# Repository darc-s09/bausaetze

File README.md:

Bausätze des OV S09
===================

Seit mehreren Jahren haben wir im Ortsverband verschiedene
Bastelaktivitäten laufen, vorranging finden diese bei Veranstaltungen
der "Technischen Sammlungen Dresden" statt, in deren Räumen sich
unsere Klubstation DL0TSD befindet.

Während der Bausatz des LED-Thermometers sein eigenes Repository hier
besitzt, hatten wir die Software und auch Dokumentation für andere
Bausätze historisch auf einem privaten Openproject-Server gehostet.
Von dort wurden sie hier nach Github migriert.

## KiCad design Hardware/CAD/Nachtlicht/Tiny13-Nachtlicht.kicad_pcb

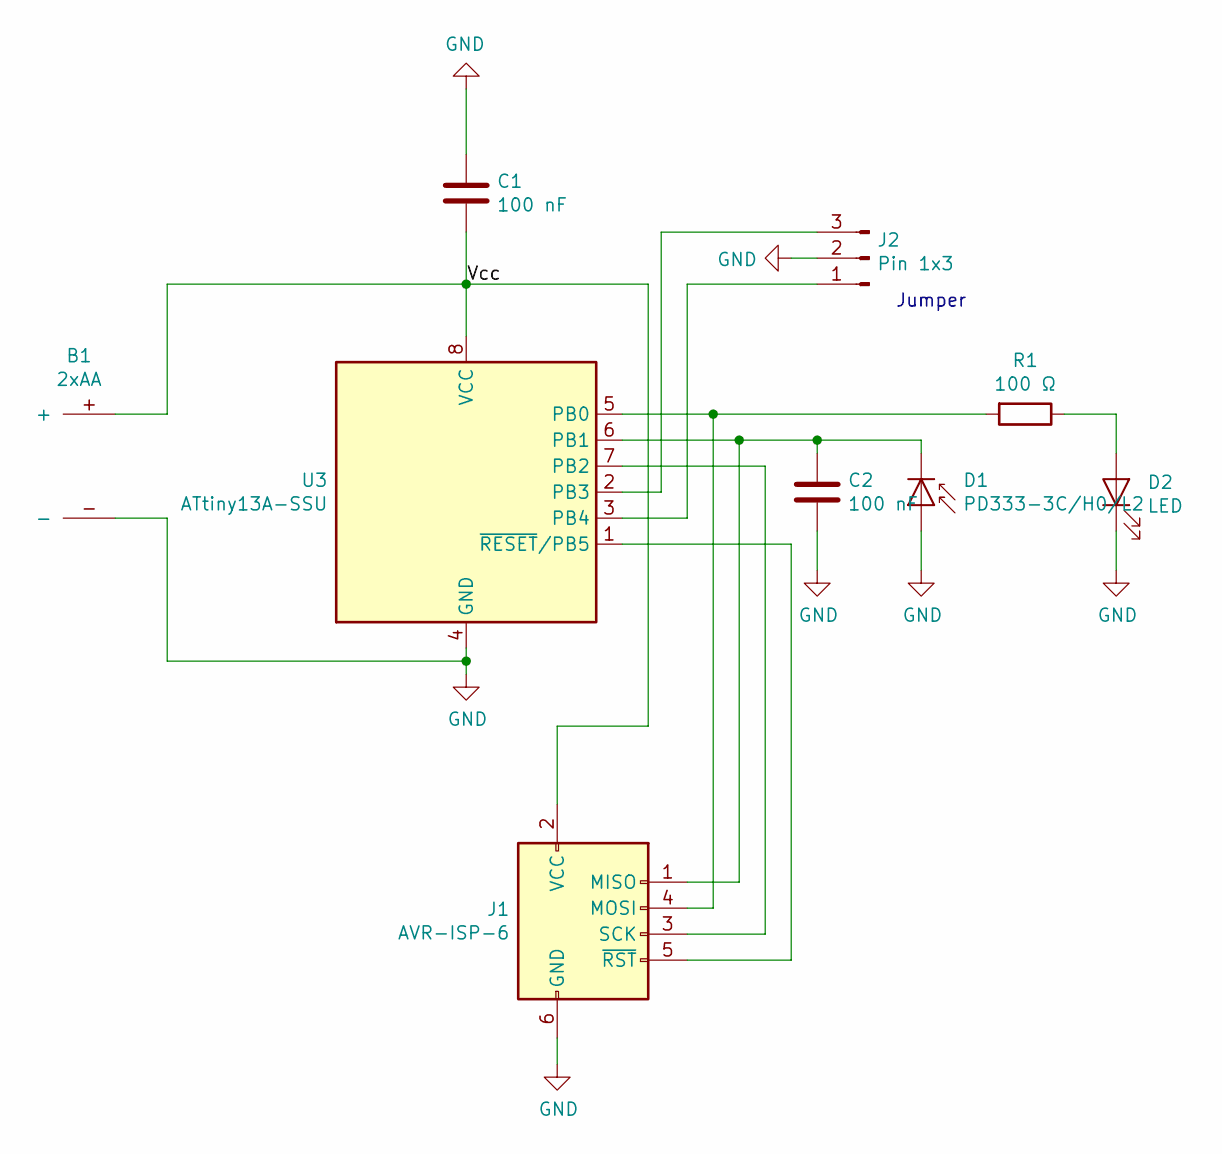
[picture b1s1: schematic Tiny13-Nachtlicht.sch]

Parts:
B1: 2xAA; 2xAA-standing
C1, C2: 100 nF; C_0805_HandSoldering
D1: PD333-3C/H0/L2; LED-5MM
D2: LED; LED-5MM
J1: AVR-ISP-6; Pin_Header_Straight_2x03
J2: Pin 1x3; Pin_Header_Straight_1x03
R1: 100 Ω; R_0805_HandSoldering
U3: ATtiny13A-SSU; SOIC-8_3.9x4.9mm_P1.27mm

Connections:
/Vcc: B1.+, C1.1, J1.2 (VCC), U3.8 (VCC)
GND: B1.-, C1.2, C2.2, D1.2 (A), D2.1 (K), J1.6 (GND), J2.2, U3.4 (GND)
unnamed: C2.1, D1.1 (K), J1.1 (MISO), U3.6 (PB1)
unnamed: D2.2 (A), R1.1
unnamed: J1.3 (SCK), U3.7 (PB2)
unnamed: J1.4 (MOSI), R1.2, U3.5 (PB0)
unnamed: J1.5 (~RST), U3.1 (~RESET~/PB5)
unnamed: J2.1, U3.3 (PB4)
unnamed: J2.3, U3.2 (PB3)

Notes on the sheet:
Jumper

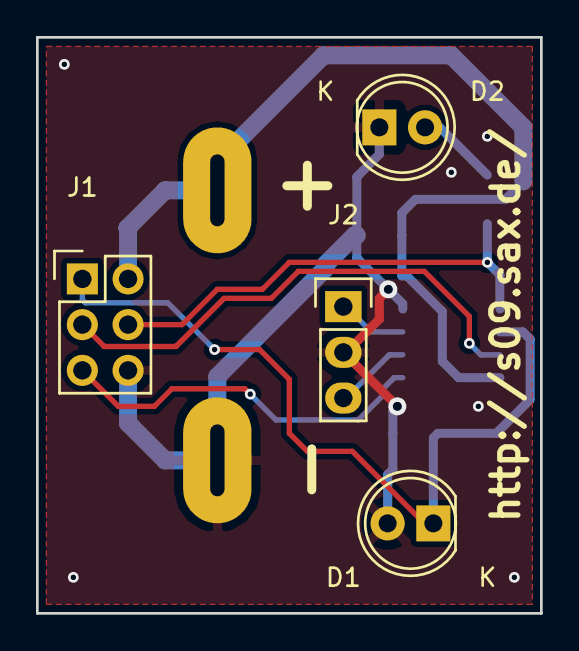
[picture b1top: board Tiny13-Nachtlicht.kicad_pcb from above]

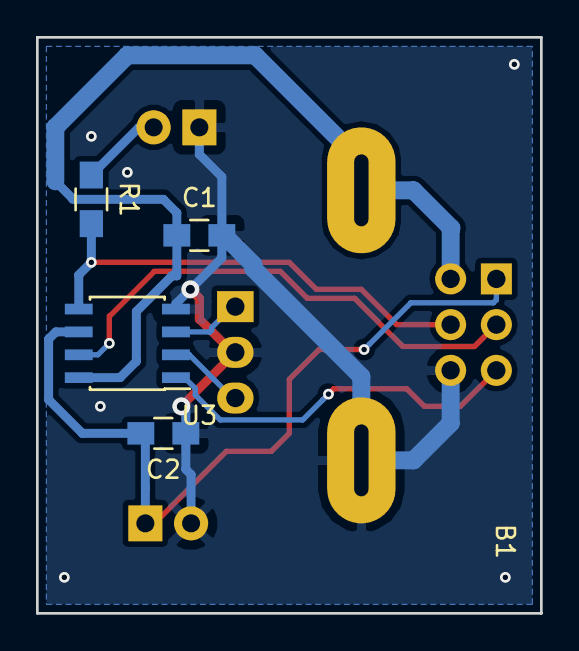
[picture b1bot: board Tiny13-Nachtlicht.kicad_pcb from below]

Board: 2 copper layers, 28.0 x 32.0 mm, 9 parts (5 on the bottom side), 9 nets.

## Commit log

2019-10-16 Create top-level structure.
2019-10-17 Create some more structure
2019-10-19 Versionstsand Januar 2019 eingestellt
2019-10-19 PDF Dateien der Schaltplaene angehangen
2019-10-21 Tabs durch Leerzeichen ersetzt, Leerzeichen am Ende der Zeile entfernt.
    Umlaute ersetzt, damit man es auch in Umgebungen lesen kann, die kein
    Latin-1 mehr benutzen.
2019-10-22 Schaltplaene ueberarbeite, Board noch nicht komplett geroutet
2019-10-24 Schaltplaene und Board in Eagel Version 7 ueberfuehrt. Gerberdateien vom aktuellen Entwicklungsstand erzeugt
2019-10-25 Sicherung eingefuegt, Gerberdateien aktualisiert
2019-10-26 Taster eingefuegt, Gerberdateien ueberarbeitet
2019-10-27 USB-Schutzschaltung,12MHZ Quarz integriert,Layout + Loetstopmake optimiert
2019-10-27 Bestückungsdruck vergrößert
2019-10-27 Noch ein wenig an der Schrift herum gefeilt
2019-10-27 Offenbar lassen sich vernünftige Strichstärken der Schrift nur mit Vektorfonts erreichen.
2019-10-28 Batchdatei fuer CAM Job und Konfiguration fuer DRC ins Projekt integriert
2019-10-28 Gerberdaten neu erzeugt nach den diversen Änderungen
    Dies ist die Produktionsfassung, die dem Fertiger in Auftrag gegeben
    wurde.
2019-11-01 c und h Files ueberarbeitet, dabei Fehler in Schaltplan gefunden, diesen beseitigt aber keine neuen Gerberdateien erzeugt
2019-11-02 Kommentare im Programm ueberarbeitet
2019-11-04 Wuerfel funktioniert, geht aber nur ueber UART anzusteuern. Taster folgt ...
2019-11-04 Einfacher Quarzfrequenz-Test: f_CPU/2 an PB3 (pin 4 ISP)
2019-11-05 Wuerfel Spezial Mode eingearbeitet
2019-11-05 Zweiten Zufallsgenerator eingebaut und Fehler Bereinigung
2019-11-06 Drop Windows .exe extensions
2019-11-06 Remove dependency directory from SVN
2019-11-07 Vorbereitung des Multiplayer Modes
2019-11-07 Add .hg to svn:ignore
2019-11-07 Add virgin bootloadHID 2012-12-08
    https://www.obdev.at/products/vusb/bootloadhid.html
2019-11-07 Update for our project
2019-11-07 Change default AVRDUDE programmer
2019-11-07 This binary is for FreeBSD.
2019-11-07 This is the Linux commandline tool
2019-11-07 Move the binaries into their own subdir
2019-11-07 Remove useless "executable" properties
2019-11-07 Move binaries into their own subdir.
2019-11-08 Switch zum Wuerfeln aktiviert, PORTC PIN 4
2019-11-11 First version of Nachtlicht
2019-11-12 Verbesserung des Multiplayer Modes
2019-11-12 Rename formal argument in ticks_to_ms()
    Using "ticks" both as formal argument as well as global
    variable was confusing.
2019-11-12 Move LED updates into the main loop, only set flag in ISR
2019-11-12 Avoid "stuck dim LED" effect
    During measurement, do not enable PWM output already. Otherwise, with
    OCR0A = 0, it resulted in a one-clock-cycle (7 µs) turn-on period of
    the LED already, causing it to be dim.
    Abort current measurement if measurement time exceeds the period
    defined for full darkness; this avoids the measurement taking
    virtually forever, so the next measurement was already triggered 10
2019-11-12 "seconds" can be made private to WDT_vect.
2019-11-12 Implement J2 1-2: dim LED jumper
2019-11-13 Vorbereitung der Funktionsauswahl ueber Jumper
2019-11-13 Add local variables, for Emacs.
2019-11-13 Move variable definitions into source file.
2019-11-13 Avoid "value computed is not used" warning
2019-11-14 Kleine Aenderung Abfrage Wuerfel Modus
2019-11-15 Implementierung der verschiedenen Wuerfel Modis abgeschlossen
2019-11-16 Move the "all" target to be the first one.
    Only that way it can work as intended.
2019-11-16 Move more variable declarations from header to source file.
2019-11-17 Ersatz von "magic numbers" durch symbolische Konstanten
2019-11-17 Entfernen der unbenutzten Funktion warte_sekunde()
2019-11-18 UART kann jetzt per UART_DEBOG 0 rausgenommen werden
2019-11-18 Auslagern aller UART-spezifischer Dinge nach uart.c.
    Auf diese Weise bleiben in thermo.c nur noch wenige #ifdefs, und
    es wird alles übersichtlicher.
2019-11-20 F_CPU auf 12 MHz
2019-11-20 12MHZ Teiler 1
2019-11-20 Don't use the timer 0 prescaler even for 12 MHz
2019-11-20 Add 1wire stuff
2019-11-20 1wire-Dateien einbinden (beispielhaft)
2019-11-20 umgestellt auf 12MHZ, counter fuer Tasterabfrage rausgenommen, Rest folgt am Donnerstag
2019-11-21 Plakat
2019-11-21 Preiskorrektur nach genauer Kalkulation
2019-11-21 counter rausgeschmissen, interne Temperaturmessung auf Interrupt umgestellt
2019-11-21 Move ow_power() into its own function
2019-11-21 Re-add Emacs local variables that vanished in r59.
    Move beer-ware license into its own paragraph.
2019-11-21 Vereinheitlichung des Einrückungs-Stils
    Keinerlei inhaltliche Änderungen.
2019-11-22 Vereinfachung des ADC-Auslesens (ADLAR benutzen)
2019-11-22 Remove unneeded files from SVN
2019-11-22 Oops, makedep.mk is still needed ...
2019-11-22 Erster Versuch für DS18B20-Einbindung als Temperatursensor
2019-11-22 Temperaturmessung doch 10bittig.
2019-11-22 Interner Temperatursensor jetzt auch über Rechnung in degC
    Damit sind der interne Sensor und der DS18B20 in der Behandlung
    gleichwertig. Nun muss nur noch die LED-Bandanzeige angepasst
    werden.
2019-11-22 Jumperabfrage begonnen, funktioniert aber nicht
2019-11-22 Do not use 1wire by now
2019-11-22 Umbau LED-Band auf generischen Bereich
2019-11-22 Untabify
2019-11-22 Fertigstellen Jumper-Erkennung
2019-11-22 Korrektur Klammersetzung bei Temperaturberechnung
    Korrektur off-by-one error LED Bandanzeige oberer Wert
2019-11-22 LED Helligkeit erhöhen
2019-11-23 Nachtlicht CAD-Daten
2019-11-23 Jumpersetting implementiert
2019-11-23 Implement flicker mode ("Kerze")
2019-11-23 "Random" tables from Fabian
2019-11-23 Random update from Fabian
2019-11-23 Power up the 1wire bus before probing
2019-11-23 Keep 1wire bus powered all the time
2019-11-23 Return actual probe result
2019-11-30 remove unneeded delay
2019-11-30 Fix order in set_dq()
2019-11-30 Preserve interrupt status in internal functions.
    Keep interrupts disabled when turning on strong pullup
2019-12-01 Bausatzbeschreibung Wuerfel begonnen
2019-12-01 Alternatives Thermometer mit 1wire-Sensor.
    Nur für den Test erstmal, um das 1wire-Setup zu debuggen. Der Code war
    ursprünglich für eine völlig andere Hardware konzipiert und wurde nur
    schnell adaptiert.
2019-12-01 Make OW_POWER_PIN an output, actually
2019-12-02 Fix value of R1 to match the one actually used.
    Add PDF of schematics, and archive of entire Kicad project.
2019-12-02 Schaltplan und Kicad-Projekt für Webseite.
2019-12-02 CAM data for Nachtlicht, as ordered at PCB factory
2019-12-02 Implement Get_ROMCode
    Currently only used when UART debugging is enabled.
2019-12-02 Implement device detection for 1wire sensors
2019-12-02 Add Configure_DS18B20()
    Configures a connected DS18B20 for 9-bit operation, so the conversion
    time can be reduced to 100 ms.
2019-12-04 Allow UART_DEBUG override from commandline
2019-12-04 Move ADC_init() into its own function
2019-12-05 Select PC3 for powering the external pull-up while probing
2019-12-05 Implement basic software calibration of internal sensor
2019-12-10 Gesonderte Build-Konfiguration mit UART Debugging.
2019-12-11 Umorganisation der Temp-Sensor-Kalibrierung
    ADC_Init() übernimmt Parameter, mit dem festgelegt wird, ob
    der ADC für eine Temperaturmessung oder für die Poti-Abfrage
    initialisiert werden soll. Im Kalibriermodus wechseln sich
    beide Betriebsarten ab.
    Die Messung erfolgt wieder durch Timer 1 gesteuert, allerdings
    schneller als im Normalbetrieb.
2019-12-11 Einstellung von Timer 1 komplett innerhalb Timer_Init()
2019-12-12 Abspeichern und Einlesen des Kalibrierwertes interner Sensor im EEPROM
2019-12-13 Do not disable power of 1wire Subsystem again
    Powering off the 1wire bus in ADC_read_ADC2() caused any potentially
    connected 1wire sensor to not be detected anymore.
    Just keep the 1wire subsystem enabled all the time.
2020-02-12 Angefangen mit der Bausatzbeschreibung Wuerfel
2024-07-18 Add a simple README
2026-03-26 Copy over sources from µracoli repo
    Use slightly different Makefile here.
2026-03-31 First attempt of adapting to re-wired boards
    Effectively, swap PB0..2 and PD5..7
    PB0..2 now used as capacitive touchpads,
    PD5..7 now used as LED column selection.
2026-04-03 Update µracoli to latest source
    This fixes a compile-time warning about an undefined macro.
2026-06-21 Fix DDRx handling
    DDRD must be initialized during startup, to enable LED outputs.
    Reading back DDRB in display_leds() is not needed.
